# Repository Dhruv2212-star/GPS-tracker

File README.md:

Ai ussage- debugging firmware  
Project description- a small pocket sized instrument that uses GPS module paired with Xiao RP2040 module as the MCU to track your coordinates every min that you can put on websites like google maps or GPS visualizer, it uses a small Li-Po battery to save some space and also prevent and hazard related to fires from damage. it also has a charging USB-c port to charge the battery and charging and protection based on TP4056. there are 3 LEDs that provide data on GPS logging, data logging and power. there is also a push button to provide the user control for stopping, starting or making event loggs. 

------------------------------------------------------------------------------------------------------------------------------------------
# Firmware flashing 

**1. Install Arduino IDE**  
   Download and install the latest ver. from the official website (avoid microsoft store ver)  
**2. Install XIAO RP2040 board support.**  
Open Arduino IDE  
File->Prefrences  
Find Additional Boards Manager URLs.  
Add:  
https://github.com/earlephilhower/arduino-pico/releases/download/global/package_rp2040_index.json  
Click Ok  
Then-  
Tools->Board->Board manager  
search- Pico  
Install- Raspberry Pi Pico/RP2040/RP2350  
**3. Connect the XIAO**  
**IF Board is *NOT* detected:**  
    1. Hold the Boot button  
    2. connect the USB  
    3. Release BOOT  
    the computer should show RPI-RP2 when the Xiao enters Bootloader mode  
**4. Select the board**  
In Arduino IDE:  
Tools->Board->Raspberry Pi RP2040 Boards_>Seeed XIAO RP2040  
Then: Tools->Port  
Select the port corresponding to your Xiao  
**5. Install TinyGPSPlus**  
The firmware i made uses:  
#include <TinyGPSPlus.h>  
Go to:  
Sketch->Include->Manage liberaries  
Search:  
**TinyGPSPlus**  
**6. Open The firmware in arduino IDE**  
**8. First compile WITHOUT the PCB**  
**9. Upload to the XIAO**  
Click: Upload   
**10. Open Serial Monitor**  
Tools-> Serial monitor  
Set: 115200 baud  
You should be able to see the following-  
Initializing microSD...  
microSD OK  
GPS Tracker ready.  
Press SW1 to START/STOP logging.  
If the GPS is **not** Connected then you might see: Fix: NO | Satellites: NA | Logging: NO  
**11. Insert the microSD card**  
When the board starts Our firmware would start as following:  
Initializing microSD...  
microSD OK  
**12. Connect the GPS antenna**  
Fix: YES | Satellites: 8 | Logging: NO  
If this is what it shows then you are good to go  
now,  
No fix > D4 OFF  

Valid fix > D4 ON  
**14. Start logging**  
Press SW1.  
Our firmware will:  

Create a new file.  
Generate like:  
**TRACK00.CSV**  
Start logging.   
Turn D5 ON.  
Record one GPS position approximately every second  
The Display should show:  
Logging STARTED  
Then,  
GPS record written.  
GPS record written  
GPS record written.  
**15. Stop logging**  
If you press SW1 again, you'll see 'Logging STOPPED'  
Our firmware flushes & closes the Recording file before stopping, which is important for preventing an unfinished CSV file.  
**16. Check the SD card**  
You should find a file named- TRACK00.CSV  
you can open it with Excel (recommended)  

Here is an example of what it will contain: **Date,Time,Latitude,Longitude,Altitude_m,Speed_kmh,Satellites**  

------------------------------------------------------------------------------------------------------------------------------------------
# Lets get into the project details and the function of each block and the components present in them! 
 ## block 1  

 1. USB-c: (J1) for charging the battery or powering the device  
 2. F1- polyfuse: protects the board from excessive input current  
 3. D1- Protects the board from input voltage spikes  
 4. R1- CC1 pulldown   
 5. R2- CC2- pulldown  
## block 2

1. TP4056 (U1): main ic for charging the battery  
2. R3- sets the charging current for battery  
3. C1- stabalises the input current from the charger's side  
4. C2- stabalizes the battery input current of the charger  
5. D2- indicates battery is charging  
6. D3- indicates that the charging is complete  
7. R4- limits D2 current to prevent it from burnout  
8. R5- Limits D3 current to prevent it from burnout  
## Block 3 

1. AP2112K-3.3 (U2): converts battery voltage-> 3.3v  
2. C2- LDO input  
3. C3- filter 3.3v  
## Block 4 

1. Rp4020 module (u3)- the MCU for the project  
2. C5- decoupling capacitor for U3   
## Block 5

1. MAX-M10S (U4): the main GPS module that recives the satalite rays 
2. C6- decoupling for U4  
3. C7additional capacitor for filtering supply  
4. J3- antena  
## Block 6  

1. SD card (J4): the storage for the cordinates that the GPS module records  
2. C8: servers as the purpose of high frequency decoupling
3. C9: servers as the purpose of 3.3v supply filtering
## Block 7 

1. D4, indicates the GPS status  
2. D5 indicates the GPS data logging    
3. D6 Indicates board power
4. R6: protect D3 from overcurrent  
5. R7: protect D4 from overcurrent
6. R8: protect D5 from overcurrent
7. SW1: For User control  

# Final product

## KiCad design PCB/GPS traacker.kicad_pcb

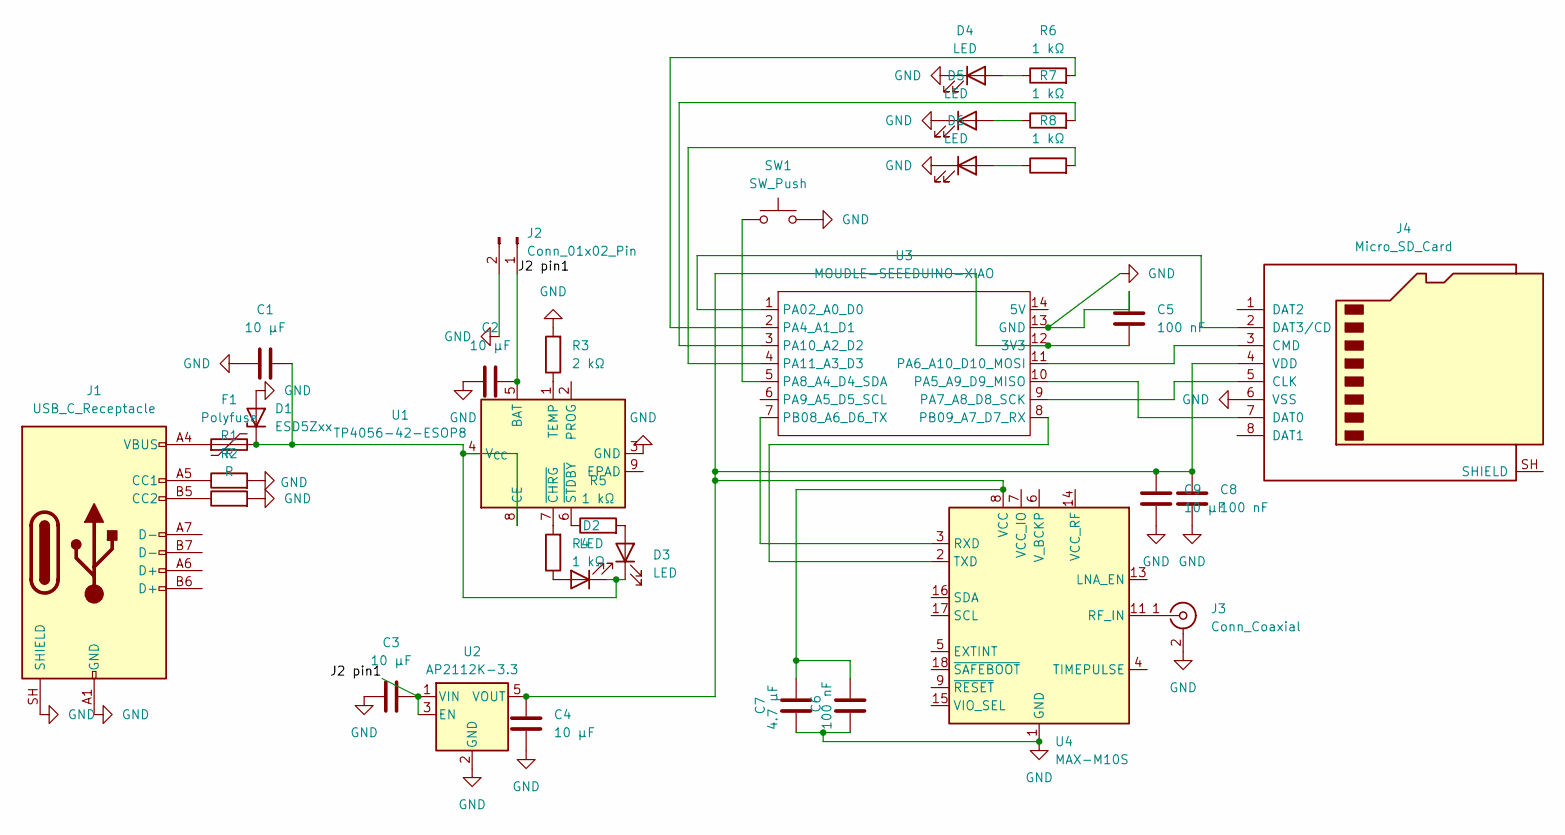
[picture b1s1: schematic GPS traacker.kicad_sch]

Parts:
C1, C2, C3, C4, C9: 10 µF; C_0603_1608Metric
C5, C6, C8: 100 nF; C_0603_1608Metric
C7: 4.7 µF; C_0603_1608Metric
D1: ESD5Zxx; D_SOD-523
D2, D3, D4, D5, D6: LED; LED_0603_1608Metric
F1: Polyfuse; Fuse_1206_3216Metric
J1: USB_C_Receptacle; USB_C_Receptacle_GCT_USB4105-xx-A_16P_TopMnt_Horizontal
J2: Conn_01x02_Pin; JST_PH_B2B-PH-K_1x02_P2.00mm_Vertical
J3: Conn_Coaxial; U.FL_Hirose_U.FL-R-SMT-1_Vertical
J4: Micro_SD_Card; microSD_HC_Hirose_DM3AT-SF-PEJM5
R1, R2: R; R_0603_1608Metric
R3: 2 kΩ; R_0603_1608Metric
R4, R5, R6, R7, R8: 1 kΩ; R_0603_1608Metric
SW1: SW_Push; SW_SPST_TL3305A
U1: TP4056-42-ESOP8; SOIC-8-1EP_3.9x4.9mm_P1.27mm_EP2.41x3.3mm_ThermalVias
U2: AP2112K-3.3; SOT-23-5
U3: MOUDLE-SEEEDUINO-XIAO; XIAO-Generic-Hybrid-14P-2.54-21X17.8MM
U4: MAX-M10S; ublox_MAX

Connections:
/J2 pin1: C2.2, C3.2, J2.1, U1.5 (BAT), U2.1 (VIN), U2.3 (EN)
GND: C1.2, C2.1, C3.1, C4.2, C5.2, C6.1, C7.1, C8.2, C9.2, D1.2 (A), D4.1 (K), D5.1 (K), D6.1 (K), J1.A1 (GND), J1.A12 (GND), J1.B1 (GND), J1.B12 (GND), J1.SH (SHIELD), J2.2, J3.2 (Ext), J4.6 (VSS), R1.2, R2.2, R3.2, SW1.2, U1.3 (GND), U2.2 (GND), U3.13 (GND), U4.1 (GND), U4.10 (GND), U4.12 (GND)
unnamed: C1.1, D1.1 (K), D2.1 (K), D3.1 (K), F1.2, U1.4 (V_{CC}), U1.8 (CE)
unnamed: D2.2 (A), R4.1
unnamed: D3.2 (A), R5.2
unnamed: D4.2 (A), R6.1
unnamed: D5.2 (A), R7.1
unnamed: D6.2 (A), R8.1
unnamed: F1.1, J1.A4 (VBUS), J1.A9 (VBUS), J1.B4 (VBUS), J1.B9 (VBUS)
unnamed: J1.A5 (CC1), R1.1
unnamed: J1.B5 (CC2), R2.1
unnamed: J3.1 (In), U4.11 (RF_IN)
unnamed: J4.5 (CLK), U3.9 (PA7_A8_D8_SCK)
unnamed: J4.3 (CMD), U3.11 (PA6_A10_D10_MOSI)
unnamed: J4.7 (DAT0), U3.10 (PA5_A9_D9_MISO)
unnamed: J4.2 (DAT3/CD), U3.1 (PA02_A0_D0)
unnamed: C4.1, C5.1, C6.2, C7.2, C8.1, C9.1, J4.4 (VDD), U2.5 (VOUT), U3.12 (3V3), U4.8 (VCC)
unnamed: R3.1, U1.1 (TEMP)
unnamed: R4.2, U1.7 (~CHRG)
unnamed: R5.1, U1.6 (~STDBY)
unnamed: R6.2, U3.2 (PA4_A1_D1)
unnamed: SW1.1, U3.5 (PA8_A4_D4_SDA)
unnamed: R7.2, U3.3 (PA10_A2_D2)
unnamed: R8.2, U3.4 (PA11_A3_D3)
unnamed: U3.7 (PB08_A6_D6_TX), U4.3 (RXD)
unnamed: U3.8 (PB09_A7_D7_RX), U4.2 (TXD)

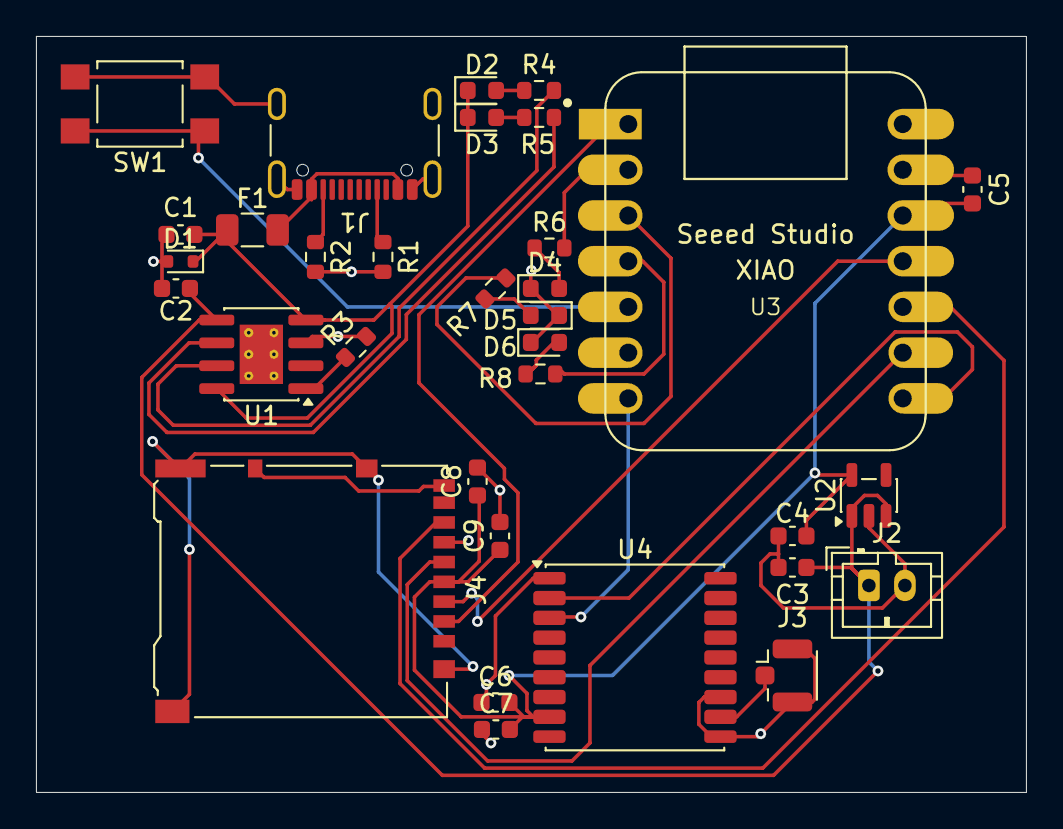
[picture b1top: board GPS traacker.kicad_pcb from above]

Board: 2 copper layers, 55.0 x 42.0 mm, 33 parts (0 on the bottom side), 26 nets.
